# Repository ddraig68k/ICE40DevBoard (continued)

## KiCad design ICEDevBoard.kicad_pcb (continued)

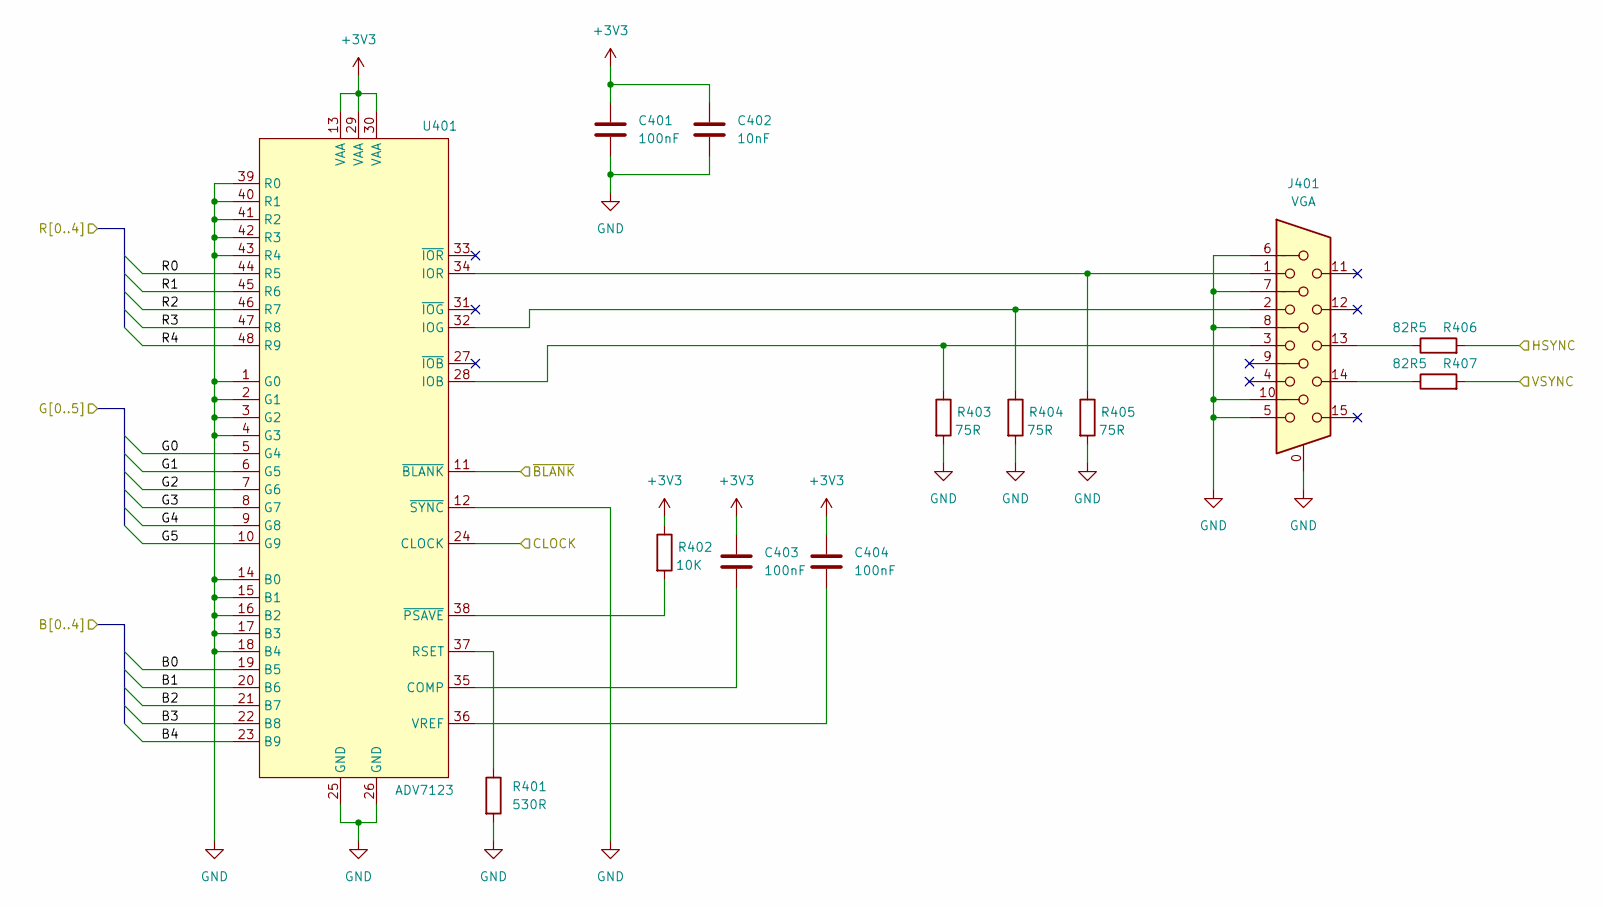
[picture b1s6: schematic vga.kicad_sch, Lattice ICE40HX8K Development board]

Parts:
C401, C403, C404: 100nF; C_0805_2012Metric
C402: 10nF; C_0805_2012Metric
J401: VGA; DSUB-15-HD_Socket_Horizontal_P2.29x2.54mm_EdgePinOffset8.35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
R401: 530R; R_0805_2012Metric
R402: 10K; R_0805_2012Metric
R403, R404, R405: 75R; R_0805_2012Metric
R406, R407: 82R5; R_0805_2012Metric
U401: ADV7123; LQFP-48_7x7mm_P0.5mm

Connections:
+3V3: C401.1, C402.1, C403.1, C404.1, R402.1, U401.13 (VAA), U401.29 (VAA), U401.30 (VAA); also elsewhere on the board
/FPGA/VGA_B0: U401.19 (B5); also elsewhere on the board
/FPGA/VGA_B1: U401.20 (B6); also elsewhere on the board
/FPGA/VGA_B2: U401.21 (B7); also elsewhere on the board
/FPGA/VGA_B3: U401.22 (B8); also elsewhere on the board
/FPGA/VGA_B4: U401.23 (B9); also elsewhere on the board
/FPGA/VGA_CLOCK: U401.24 (CLOCK); also elsewhere on the board
/FPGA/VGA_G0: U401.5 (G4); also elsewhere on the board
/FPGA/VGA_G1: U401.6 (G5); also elsewhere on the board
/FPGA/VGA_G2: U401.7 (G6); also elsewhere on the board
/FPGA/VGA_G3: U401.8 (G7); also elsewhere on the board
/FPGA/VGA_G4: U401.9 (G8); also elsewhere on the board
/FPGA/VGA_G5: U401.10 (G9); also elsewhere on the board
/FPGA/VGA_HSYNC: R406.2; also elsewhere on the board
/FPGA/VGA_R0: U401.44 (R5); also elsewhere on the board
/FPGA/VGA_R1: U401.45 (R6); also elsewhere on the board
/FPGA/VGA_R2: U401.46 (R7); also elsewhere on the board
/FPGA/VGA_R3: U401.47 (R8); also elsewhere on the board
/FPGA/VGA_R4: U401.48 (R9); also elsewhere on the board
/FPGA/VGA_VSYNC: R407.2; also elsewhere on the board
/FPGA/~VGA_BLANK: U401.11 (~BLANK); also elsewhere on the board
GND: C401.2, C402.2, J401.0, J401.5, J401.6, J401.7, J401.8, J401.10, R401.2, R403.2, R404.2, R405.2, U401.1 (G0), U401.2 (G1), U401.3 (G2), U401.4 (G3), U401.12 (~SYNC), U401.14 (B0), U401.15 (B1), U401.16 (B2), U401.17 (B3), U401.18 (B4), U401.25 (GND), U401.26 (GND), U401.39 (R0), U401.40 (R1), U401.41 (R2), U401.42 (R3), U401.43 (R4); also elsewhere on the board
unnamed: J401.13, R406.1
unnamed: J401.14, R407.1
unnamed: C403.2, U401.35 (COMP)
unnamed: J401.3, R403.1, U401.28 (IOB)
unnamed: J401.2, R404.1, U401.32 (IOG)
unnamed: J401.1, R405.1, U401.34 (IOR)
unnamed: R401.1, U401.37 (RSET)
unnamed: C404.2, U401.36 (VREF)
unnamed: R402.2, U401.38 (~PSAVE)

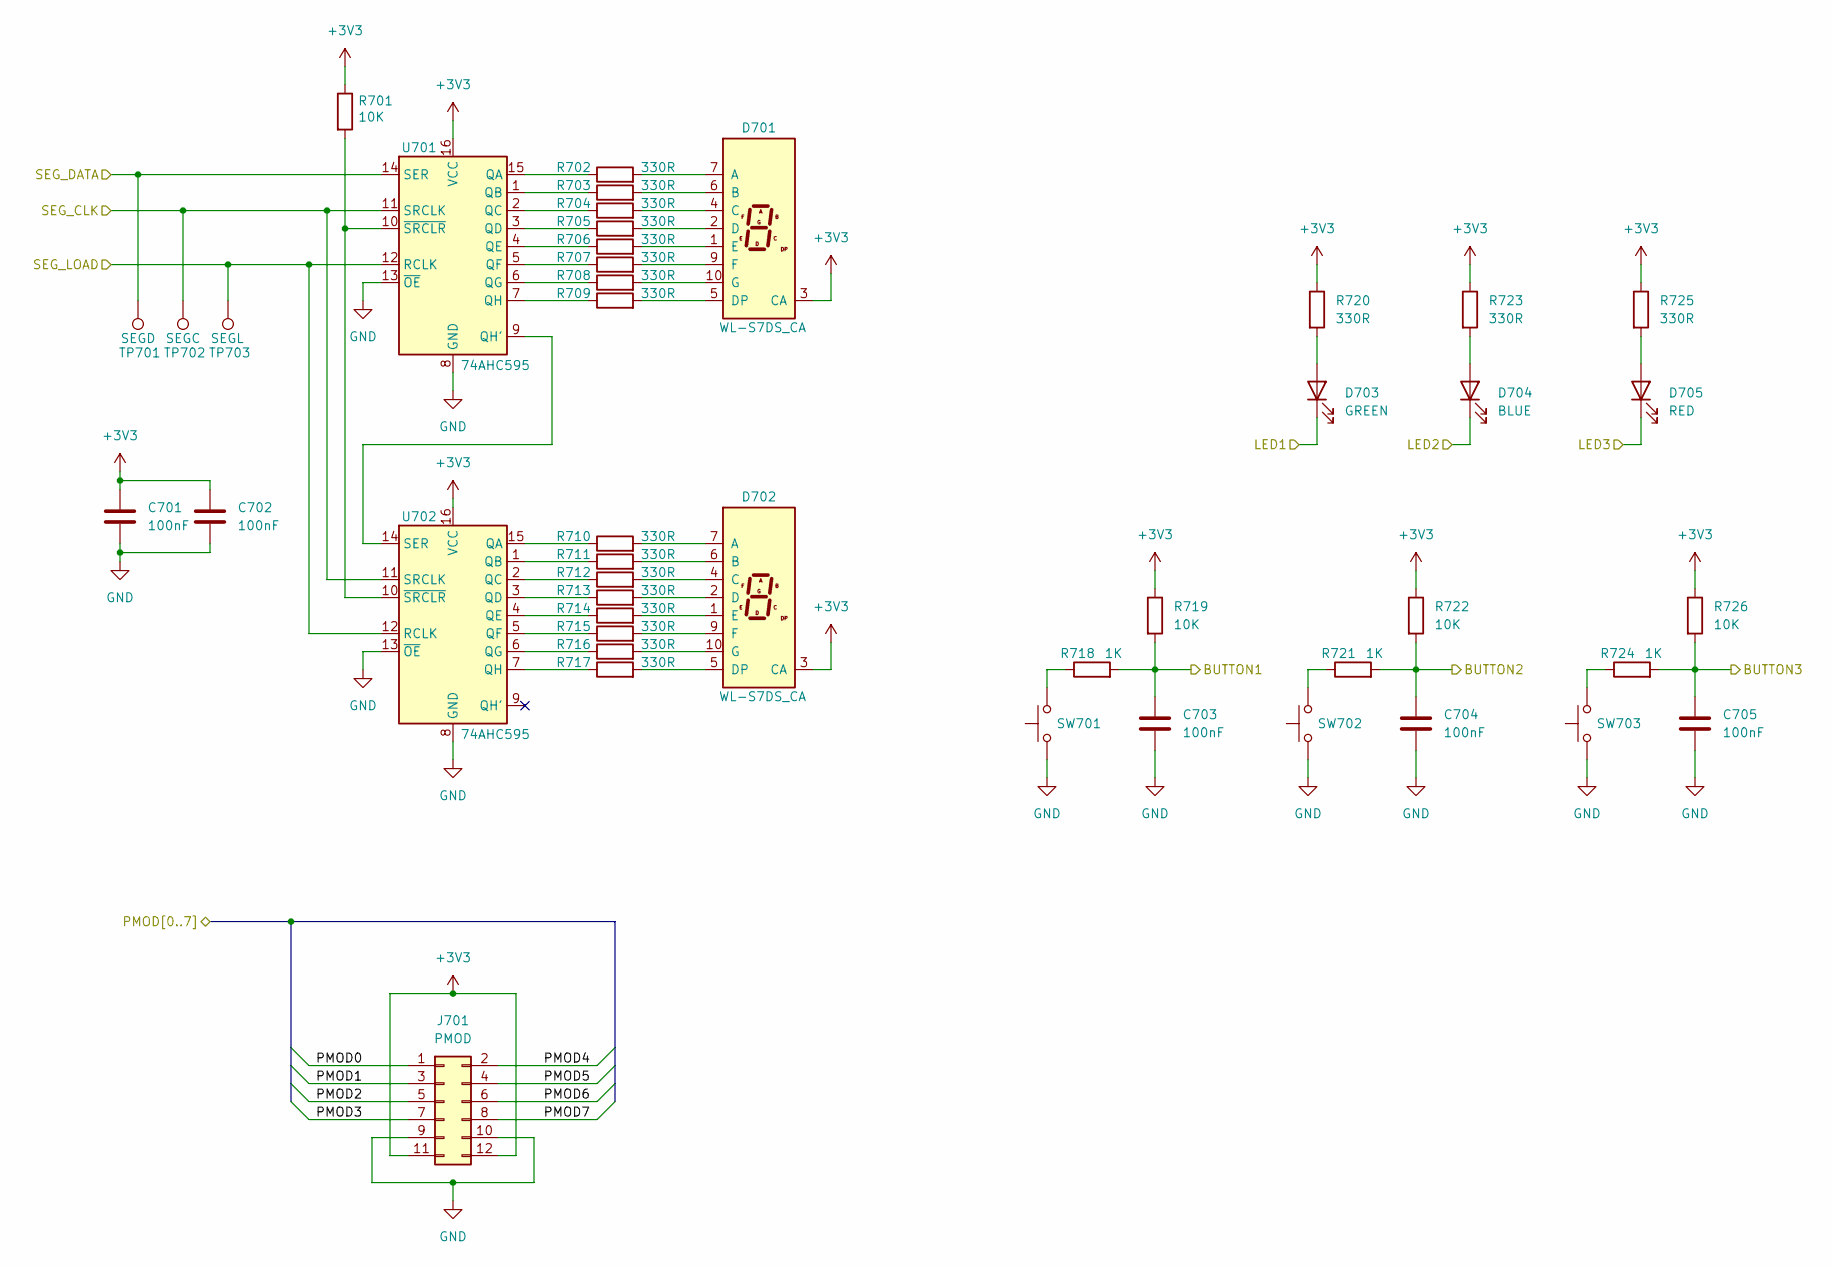
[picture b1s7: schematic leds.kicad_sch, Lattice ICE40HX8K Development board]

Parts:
C701, C702, C703, C704, C705: 100nF; C_0805_2012Metric
D701, D702: WL-S7DS_CA; WL-S7DS_0.3INCH
D703: GREEN; LED_1206_3216Metric
D704: BLUE; LED_1206_3216Metric
D705: RED; LED_1206_3216Metric
J701: PMOD; PinSocket_2x06_P2.54mm_Vertical
R701, R719, R722, R726: 10K; R_0805_2012Metric
R702, R703, R704, R705, R706, R707, R708, R709, R710, R711, R712, R713, R714, R715, R716, R717, R720, R723, R725: 330R; R_0805_2012Metric
R718, R721, R724: 1K; R_0805_2012Metric
SW701, SW702, SW703: SW_Push; SW_PUSH_6mm_H4.3mm
TP701: SEGD; TestPoint_Pad_D1.0mm
TP702: SEGC; TestPoint_Pad_D1.0mm
TP703: SEGL; TestPoint_Pad_D1.0mm
U701, U702: 74AHC595; SO-16_3.9x9.9mm_P1.27mm

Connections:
+3V3: C701.1, C702.1, D701.3 (CA), D702.3 (CA), J701.11, J701.12, R701.1, R719.1, R720.1, R722.1, R723.1, R725.1, R726.1, U701.16 (VCC), U702.16 (VCC); also elsewhere on the board
/FPGA/BUTTON1: C703.1, R718.2, R719.2; also elsewhere on the board
/FPGA/BUTTON2: C704.1, R721.2, R722.2; also elsewhere on the board
/FPGA/BUTTON3: C705.1, R724.2, R726.2; also elsewhere on the board
/FPGA/LED1: D703.1 (K); also elsewhere on the board
/FPGA/LED2: D704.1 (K); also elsewhere on the board
/FPGA/LED3: D705.1 (K); also elsewhere on the board
/FPGA/PMOD0: J701.1; also elsewhere on the board
/FPGA/PMOD1: J701.3; also elsewhere on the board
/FPGA/PMOD2: J701.5; also elsewhere on the board
/FPGA/PMOD3: J701.7; also elsewhere on the board
/FPGA/PMOD4: J701.2; also elsewhere on the board
/FPGA/PMOD5: J701.4; also elsewhere on the board
/FPGA/PMOD6: J701.6; also elsewhere on the board
/FPGA/PMOD7: J701.8; also elsewhere on the board
/FPGA/SEG_CLK: TP702.1, U701.11 (SRCLK), U702.11 (SRCLK); also elsewhere on the board
/FPGA/SEG_DATA: TP701.1, U701.14 (SER); also elsewhere on the board
/FPGA/SEG_LOAD: TP703.1, U701.12 (RCLK), U702.12 (RCLK); also elsewhere on the board
GND: C701.2, C702.2, C703.2, C704.2, C705.2, J701.9, J701.10, SW701.2, SW702.2, SW703.2, U701.8 (GND), U701.13 (~OE), U702.8 (GND), U702.13 (~OE); also elsewhere on the board
unnamed: D701.7 (A), R702.2
unnamed: D701.6 (B), R703.2
unnamed: D701.4 (C), R704.2
unnamed: D701.2 (D), R705.2
unnamed: D701.5 (DP), R709.2
unnamed: D701.1 (E), R706.2
unnamed: D701.9 (F), R707.2
unnamed: D701.10 (G), R708.2
unnamed: D702.7 (A), R710.2
unnamed: D702.6 (B), R711.2
unnamed: D702.4 (C), R712.2
unnamed: D702.2 (D), R713.2
unnamed: D702.5 (DP), R717.2
unnamed: D702.1 (E), R714.2
unnamed: D702.9 (F), R715.2
unnamed: D702.10 (G), R716.2
unnamed: D703.2 (A), R720.2
unnamed: D704.2 (A), R723.2
unnamed: D705.2 (A), R725.2
unnamed: R718.1, SW701.1
unnamed: R721.1, SW702.1
unnamed: R724.1, SW703.1
unnamed: R702.1, U701.15 (QA)
unnamed: R703.1, U701.1 (QB)
unnamed: R704.1, U701.2 (QC)
unnamed: R705.1, U701.3 (QD)
unnamed: R706.1, U701.4 (QE)
unnamed: R707.1, U701.5 (QF)
unnamed: R708.1, U701.6 (QG)
unnamed: U701.9 (QH'), U702.14 (SER)
unnamed: R709.1, U701.7 (QH)
unnamed: R701.2, U701.10 (~SRCLR), U702.10 (~SRCLR)
unnamed: R710.1, U702.15 (QA)
unnamed: R711.1, U702.1 (QB)
unnamed: R712.1, U702.2 (QC)
unnamed: R713.1, U702.3 (QD)
unnamed: R714.1, U702.4 (QE)
unnamed: R715.1, U702.5 (QF)
unnamed: R716.1, U702.6 (QG)
unnamed: R717.1, U702.7 (QH)

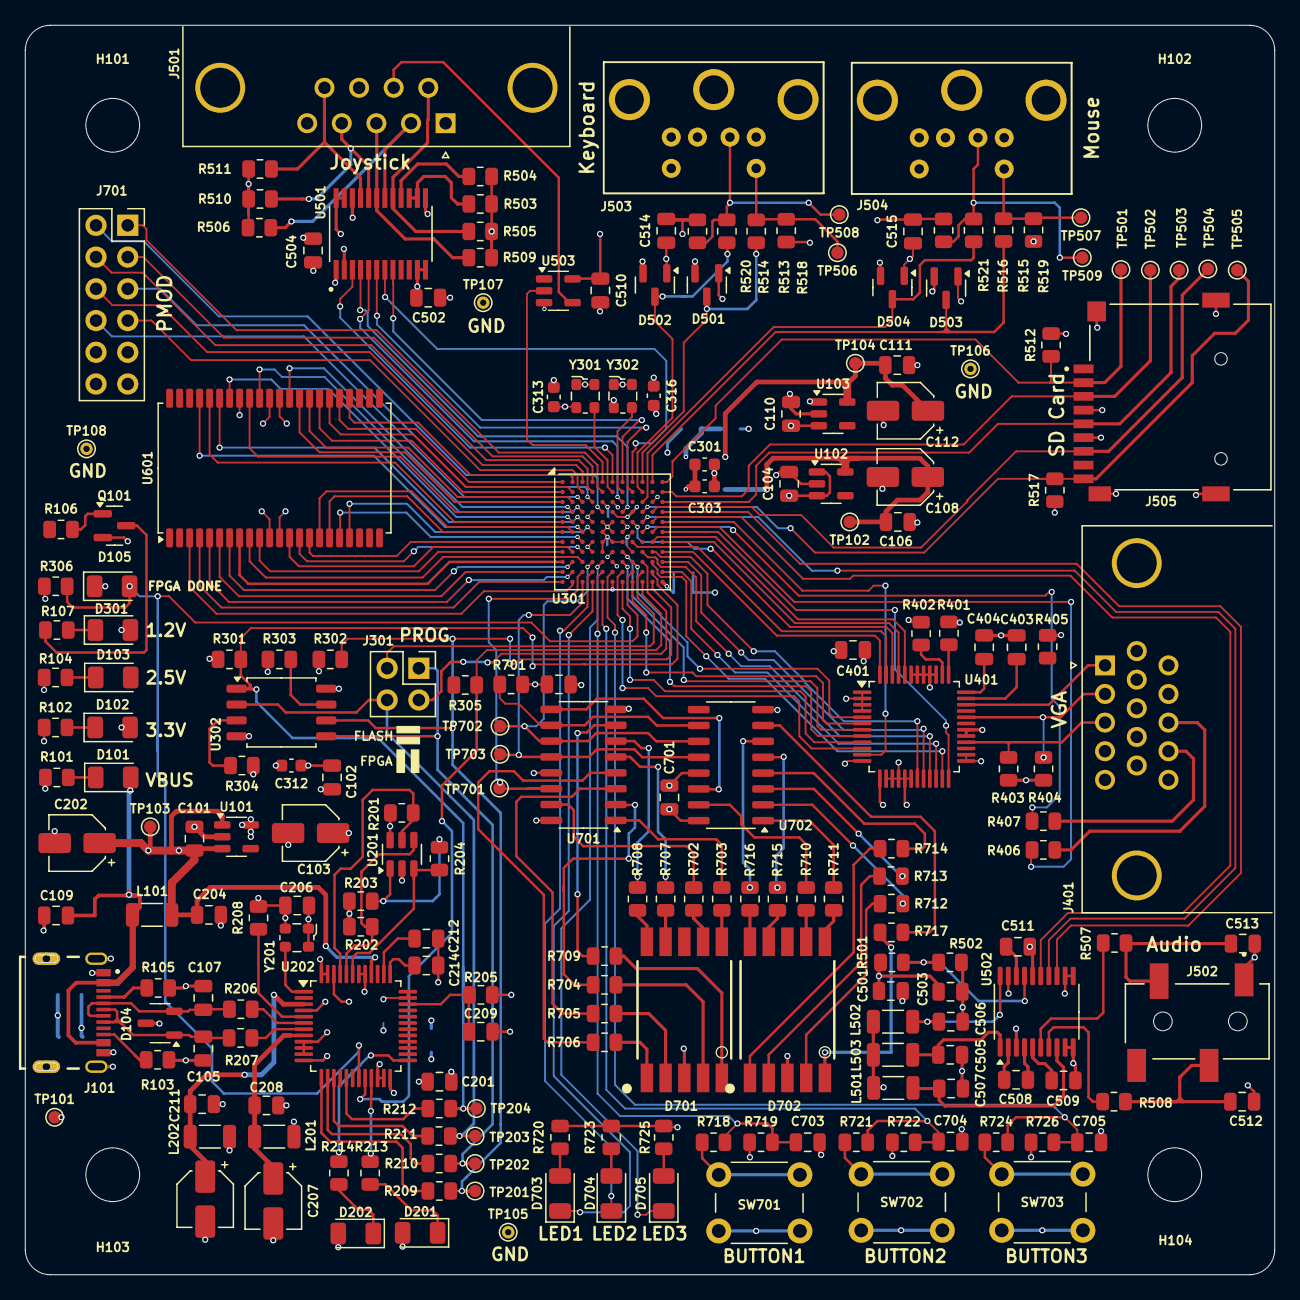
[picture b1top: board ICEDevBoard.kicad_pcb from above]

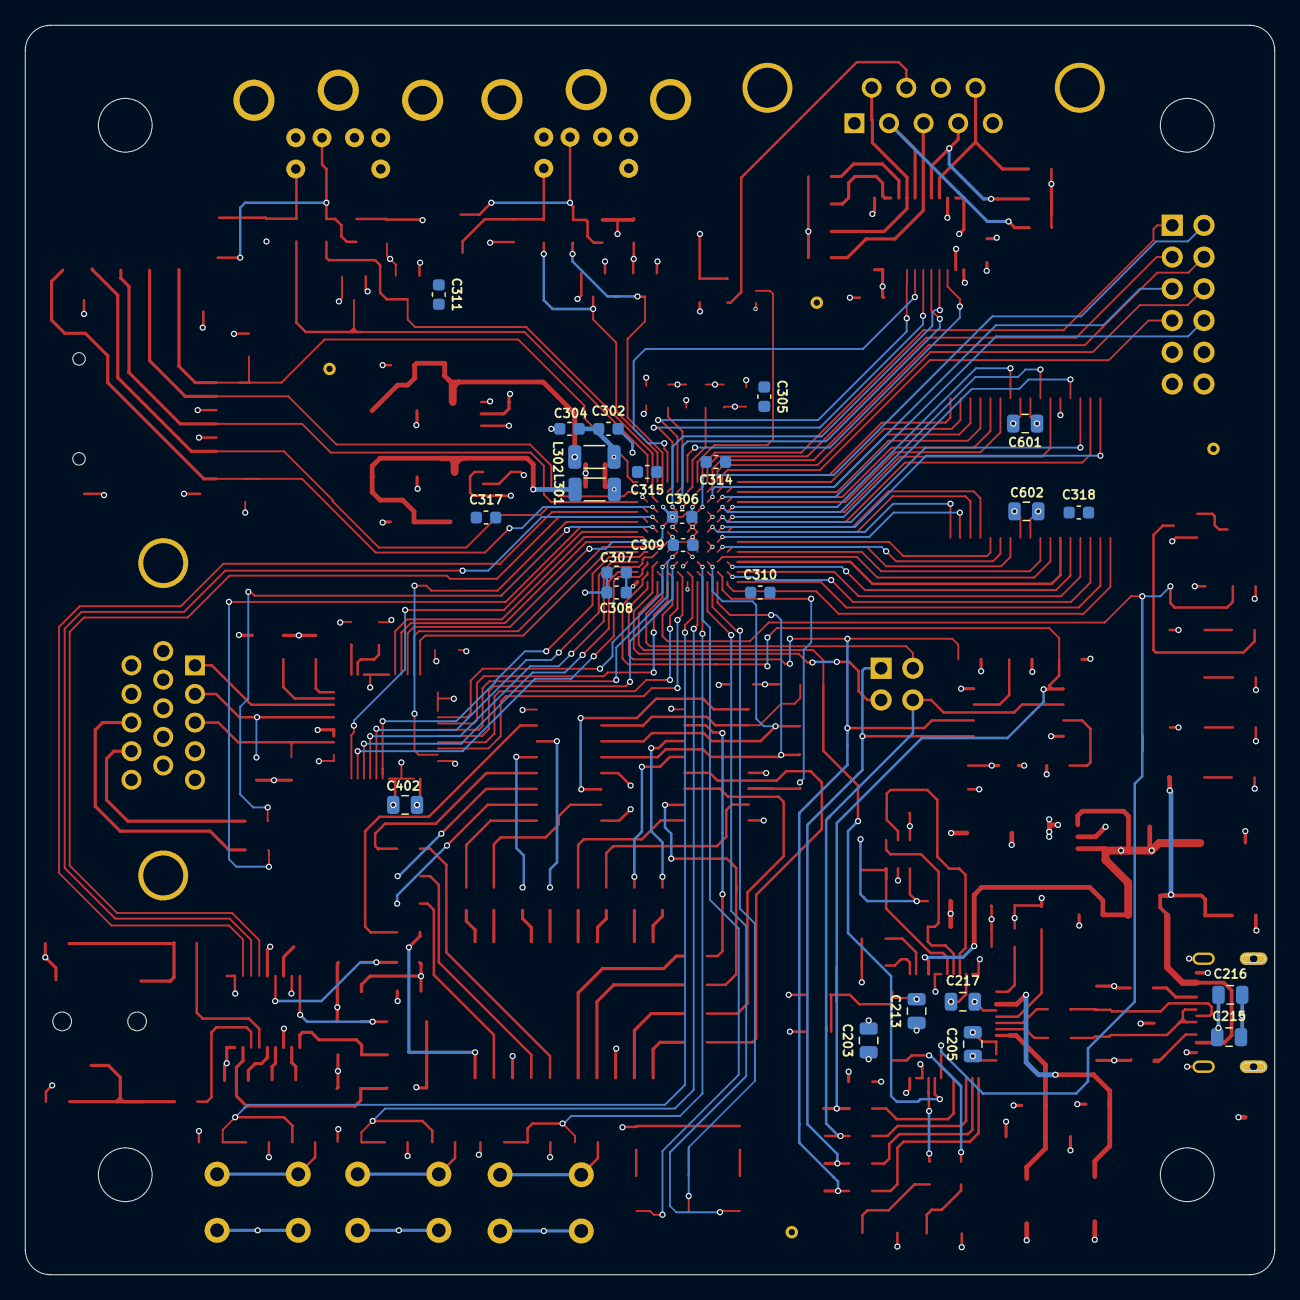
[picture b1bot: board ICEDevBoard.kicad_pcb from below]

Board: 4 copper layers, 100.0 x 100.0 mm, 237 parts (24 on the bottom side), 209 nets.

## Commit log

2025-04-26 Initial schematic design
2025-05-03 Started layout
2025-05-03 Working on board layout
2025-05-03 More board layout
2025-05-03 Started FPGA fanout
2025-05-03 Updated constraints
2025-05-04 All pins fed out of FPGA
2025-05-05 Working on layout
2025-05-05 Initial FPGA layout done
2025-05-05 Started board routing
2025-05-06 Routed SRAM
2025-05-07 Additional routing
2025-05-07 More layout done
2025-05-14 More layout changes
2025-05-14 Reworking layout
2025-05-16 Latest changes
